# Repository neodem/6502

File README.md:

# 6502
For holding my 6502 code and files

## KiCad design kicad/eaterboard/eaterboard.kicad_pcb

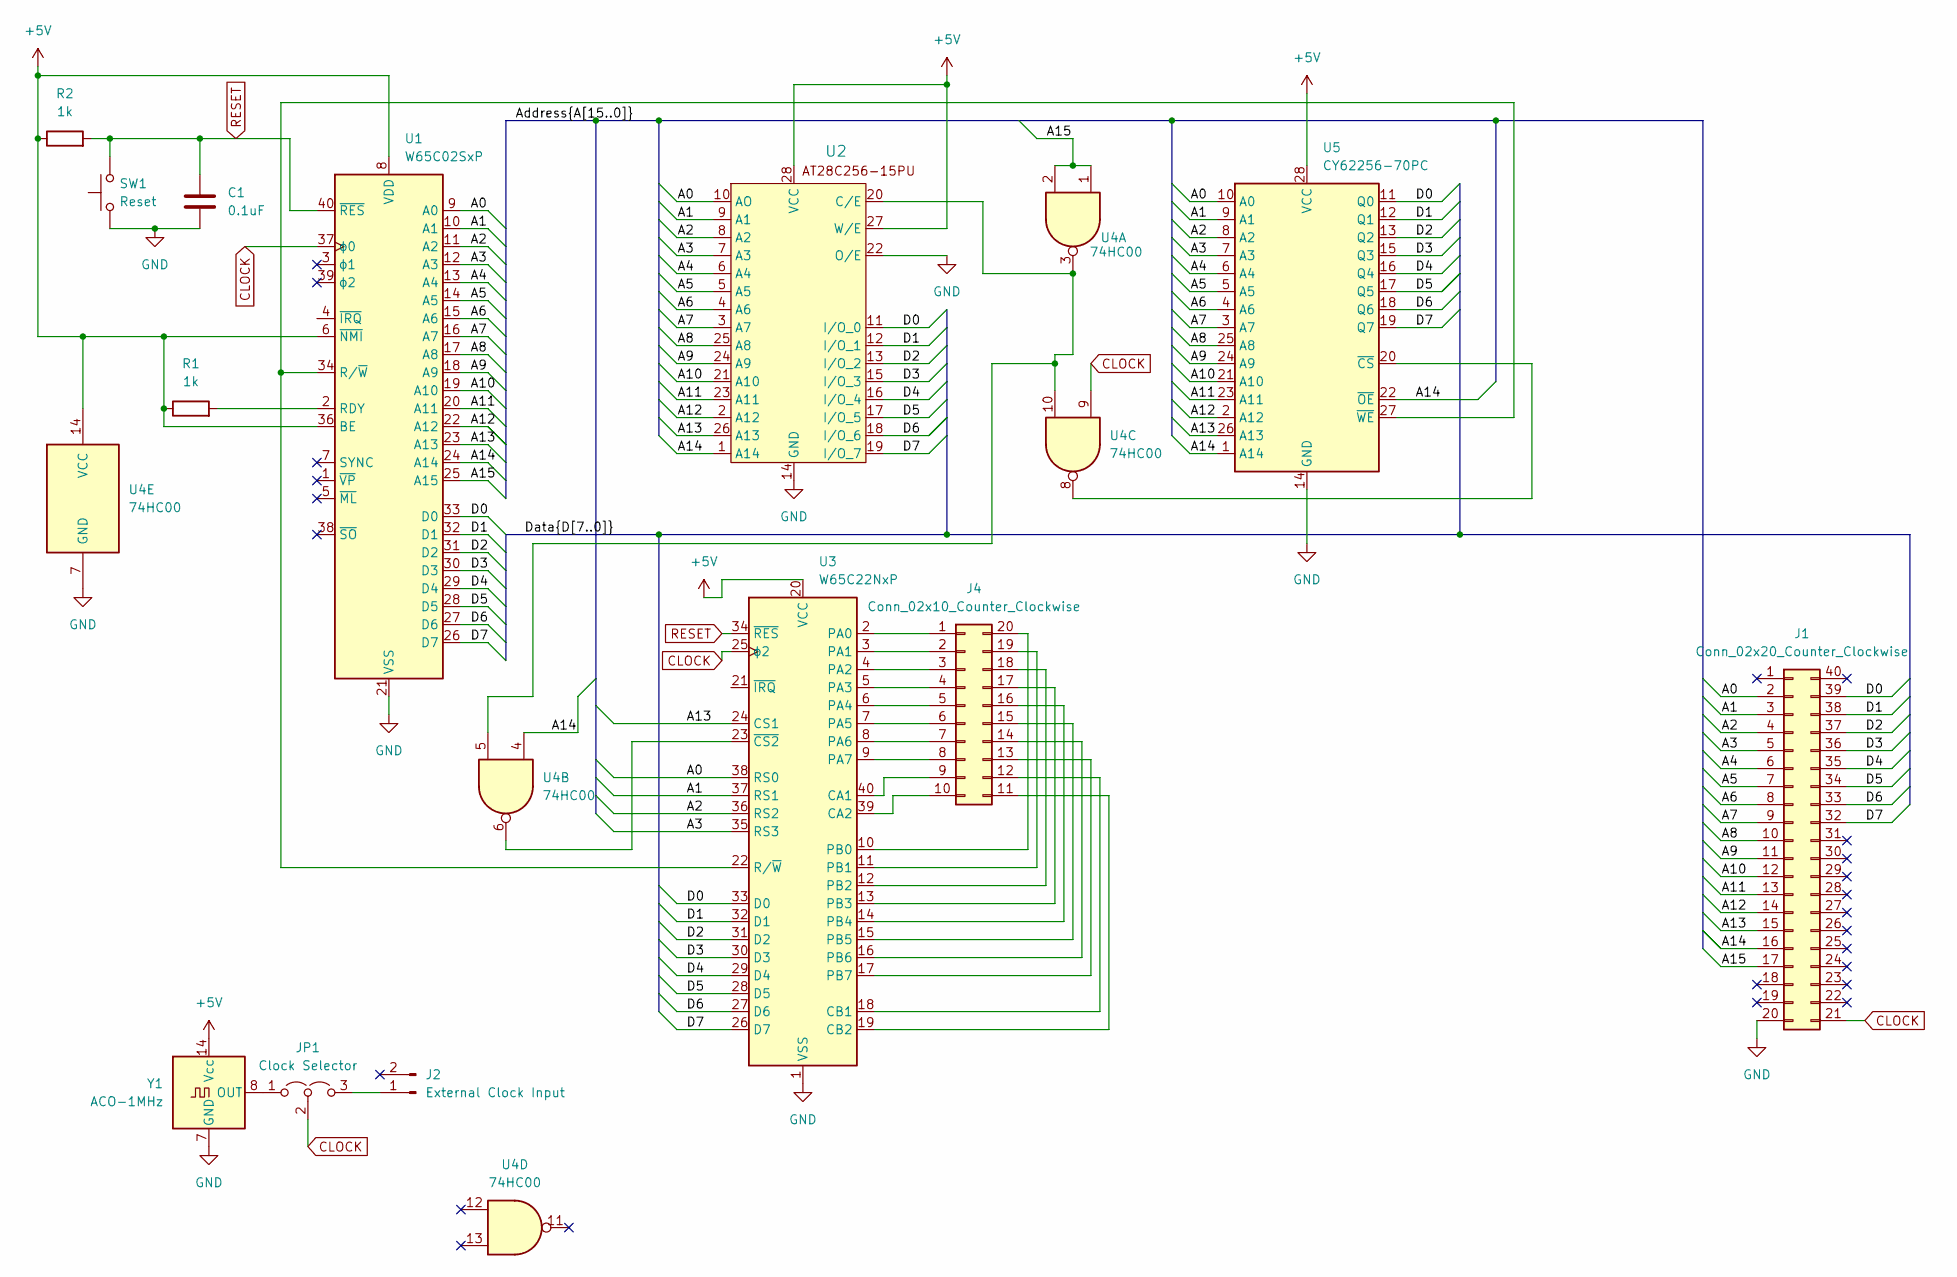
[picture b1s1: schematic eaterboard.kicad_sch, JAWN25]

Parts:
C1: 0.1uF; CP_EIA-1608-08_AVX-J
J1: Conn_02x20_Counter_Clockwise; PinSocket_2x20_P2.54mm_Vertical_SMD
J2: External Clock Input; PinSocket_1x02_P2.54mm_Vertical
J4: Conn_02x10_Counter_Clockwise; PinSocket_2x10_P2.54mm_Vertical_SMD
JP1: Clock Selector; SolderJumper-2_P1.3mm_Bridged2Bar_Pad1.0x1.5mm
R1, R2: 1k; R_Axial_DIN0204_L3.6mm_D1.6mm_P1.90mm_Vertical
SW1: Reset; KSA_Tactile_SPST
U1: W65C02SxP; DIP-40_W15.24mm
U2: AT28C256-15PU; DIP-28_W15.24mm
U3: W65C22NxP; DIP-40_W15.24mm
U4: 74HC00; DIP-14_W7.62mm
U5: CY62256-70PC; DIP-28_W15.24mm
Y1: ACO-1MHz; Oscillator_DIP-14

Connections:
+5V: R1.1, R2.1, U1.6 (~NMI), U1.8 (VDD), U1.36 (BE), U2.27 (W/E), U2.28 (VCC), U3.20 (VCC), U4.14 (VCC), U5.28 (VCC), Y1.14 (Vcc)
/A0: J1.2, U1.9 (A0), U2.10 (AO), U3.38 (RS0), U5.10 (A0)
/A1: J1.3, U1.10 (A1), U2.9 (A1), U3.37 (RS1), U5.9 (A1)
/A2: J1.4, U1.11 (A2), U2.8 (A2), U3.36 (RS2), U5.8 (A2)
/A3: J1.5, U1.12 (A3), U2.7 (A3), U3.35 (RS3), U5.7 (A3)
/A4: J1.6, U1.13 (A4), U2.6 (A4), U5.6 (A4)
/A5: J1.7, U1.14 (A5), U2.5 (A5), U5.5 (A5)
/A6: J1.8, U1.15 (A6), U2.4 (A6), U5.4 (A6)
/A7: J1.9, U1.16 (A7), U2.3 (A7), U5.3 (A7)
/A8: J1.10, U1.17 (A8), U2.25 (A8), U5.25 (A8)
/A9: J1.11, U1.18 (A9), U2.24 (A9), U5.24 (A9)
/A10: J1.12, U1.19 (A10), U2.21 (A10), U5.21 (A10)
/A11: J1.13, U1.20 (A11), U2.23 (A11), U5.23 (A11)
/A12: J1.14, U1.22 (A12), U2.2 (A12), U5.2 (A12)
/A13: J1.15, U1.23 (A13), U2.26 (A13), U3.24 (CS1), U5.26 (A13)
/A14: J1.16, U1.24 (A14), U2.1 (A14), U4.4, U5.1 (A14), U5.22 (~OE)
/A15: J1.17, U1.25 (A15), U4.1, U4.2
/D0: J1.39, U1.33 (D0), U2.11 (I/O_0), U3.33 (D0), U5.11 (Q0)
/D1: J1.38, U1.32 (D1), U2.12 (I/O_1), U3.32 (D1), U5.12 (Q1)
/D2: J1.37, U1.31 (D2), U2.13 (I/O_2), U3.31 (D2), U5.13 (Q2)
/D3: J1.36, U1.30 (D3), U2.15 (I/O_3), U3.30 (D3), U5.15 (Q3)
/D4: J1.35, U1.29 (D4), U2.16 (I/O_4), U3.29 (D4), U5.16 (Q4)
/D5: J1.34, U1.28 (D5), U2.17 (I/O_5), U3.28 (D5), U5.17 (Q5)
/D6: J1.33, U1.27 (D6), U2.18 (I/O_6), U3.27 (D6), U5.18 (Q6)
/D7: J1.32, U1.26 (D7), U2.19 (I/O_7), U3.26 (D7), U5.19 (Q7)
CLOCK: J1.21, JP1.2 (C), U1.37 (ϕ0), U3.25 (ϕ2), U4.9
GND: C1.2, J1.20, SW1.1, U1.21 (VSS), U2.14 (GND), U2.22 (O/E), U3.1 (VSS), U4.7 (GND), U5.14 (GND), Y1.7 (GND)
unnamed: J2.1, JP1.3 (B)
unnamed: J4.1, U3.2 (PA0)
unnamed: J4.2, U3.3 (PA1)
unnamed: J4.3, U3.4 (PA2)
unnamed: J4.4, U3.5 (PA3)
unnamed: J4.5, U3.6 (PA4)
unnamed: J4.6, U3.7 (PA5)
unnamed: J4.7, U3.8 (PA6)
unnamed: J4.8, U3.9 (PA7)
unnamed: J4.9, U3.40 (CA1)
unnamed: J4.10, U3.39 (CA2)
unnamed: J4.11, U3.19 (CB2)
unnamed: J4.12, U3.18 (CB1)
unnamed: J4.13, U3.17 (PB7)
unnamed: J4.14, U3.16 (PB6)
unnamed: J4.15, U3.15 (PB5)
unnamed: J4.16, U3.14 (PB4)
unnamed: J4.17, U3.13 (PB3)
unnamed: J4.18, U3.12 (PB2)
unnamed: J4.19, U3.11 (PB1)
unnamed: J4.20, U3.10 (PB0)
unnamed: JP1.1 (A), Y1.8 (OUT)
unnamed: R1.2, U1.2 (RDY)
unnamed: U1.34 (R/~W), U3.22 (R/~W), U5.27 (~WE)
unnamed: U2.20 (C/E), U4.3, U4.5, U4.10
unnamed: U3.23 (~CS2), U4.6
unnamed: U4.8, U5.20 (~CS)
RESET: C1.1, R2.2, SW1.2, U1.40 (~RES), U3.34 (~RES)

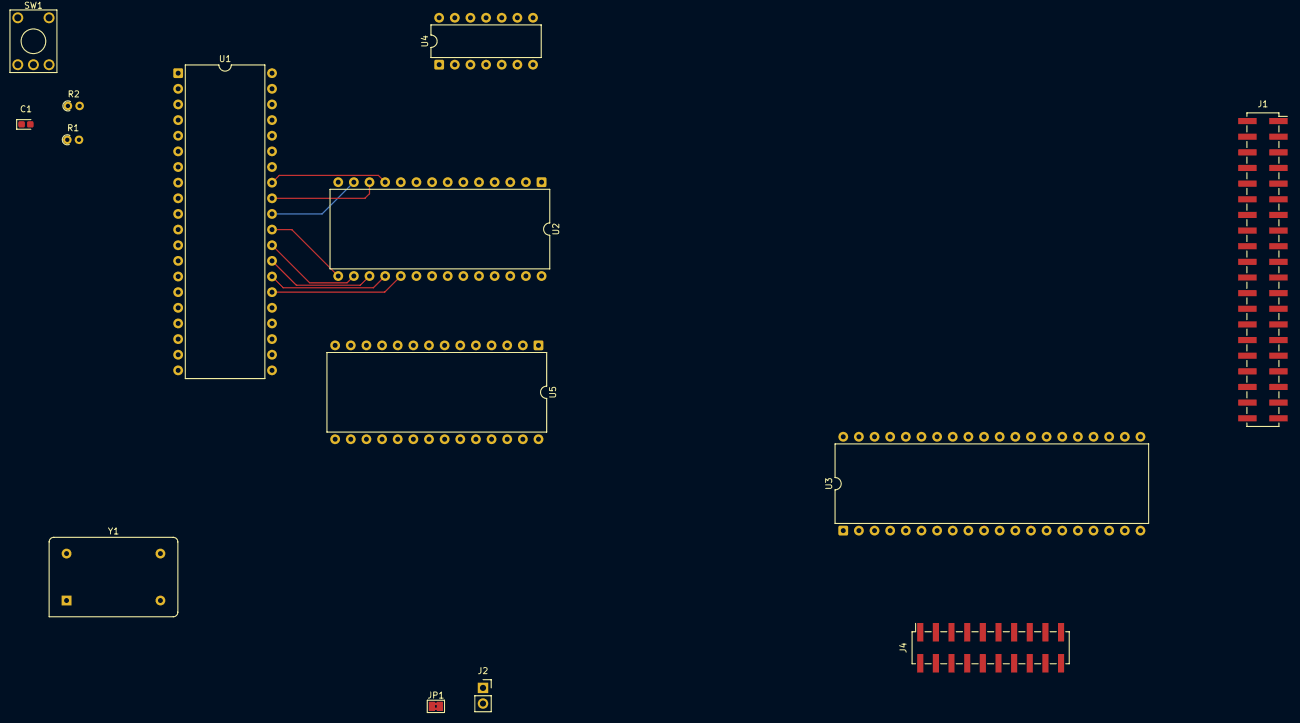
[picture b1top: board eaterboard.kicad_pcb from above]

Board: 2 copper layers, 14 parts (0 on the bottom side), 54 nets.

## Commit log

2025-03-01 initial
2025-03-02 some more stuff
